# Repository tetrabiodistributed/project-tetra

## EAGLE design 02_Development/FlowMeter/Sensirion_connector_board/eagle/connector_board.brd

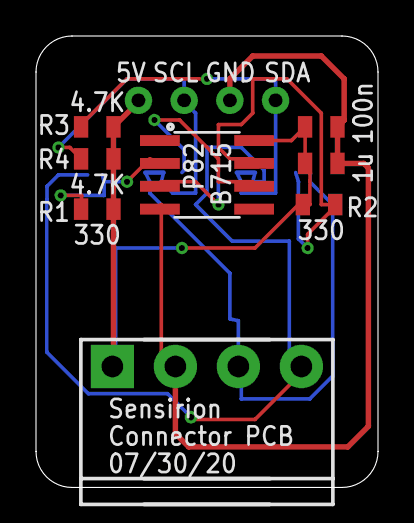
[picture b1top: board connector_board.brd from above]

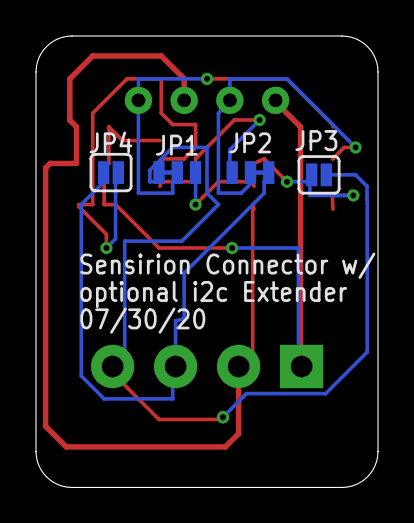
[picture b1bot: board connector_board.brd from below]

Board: 2 copper layers, 19.0 x 25.1 mm, 13 parts (4 on the bottom side), 10 nets.

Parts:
C1: 1u; 0805
C12: 100n; 0805
J2: 1X04_30MILL_DIA
J7: 1X04_3.5MM_RA
JP1, JP2: JUMPER-SMT_3_1-NC_TRACE_NO-SILK; SMT-JUMPER_3_1-NC_TRACE_NO-SILK
JP3, JP4: JUMPER-SMT_2_NO_SILK; SMT-JUMPER_2_NO_SILK
R1, R2: 330; 0805
R3, R4: 4.7K; 0805
U$2: P82B715; SOIC8

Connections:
5V: C1.1, C12.1, J2.1, J7.1, R1.2, R2.2, R3.2, R4.2, U$2.8
GND: C1.2, C12.2, J2.3, J7.2, U$2.4
LX: JP3.2, R1.1, U$2.2
LY: JP4.2, R2.1, U$2.7
SCL0: J2.2, JP2.2, R4.1
SCL1: J7.3, JP2.3, JP4.1
SDA0: J2.4, JP1.2, R3.1
SDA1: J7.4, JP1.3, JP3.1
SX: JP1.1, U$2.3
SY: JP2.1, U$2.6

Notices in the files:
parts and their libraries:
SparkFun-Jumpers: Licensing: Creative Commons ShareAlike 4.0 International - https://creativecommons.org/licenses/by-sa/4.0
